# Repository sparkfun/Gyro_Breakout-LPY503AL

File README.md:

SparkFun Gyro Breakout - LPY503AL (Dual 30°/s)
========================================

[*SparkFun Gyro Breakout - LPY503AL (Dual 30°/s) (SEN-11341)*](https://www.sparkfun.com/products/11341)

This is a breakout board for the ST’s dual-axis LPY503AL gyro.  
The LPY503AL is a MEMS motion sensor that measures angular velocity along the pitch and yaw axes with a full scale of ±30°/s. 
Two different analog outputs are provided for both the x- and z- axes - one 1x amplified and the other 4x amplified.

Repository Contents
-------------------

* **/Hardware** - Eagle design files (.brd, .sch)
* **/Production** - Production panel files (.brd)

Documentation
--------------
* **[SparkFun Fritzing repo](https://github.com/sparkfun/Fritzing_Parts)** - Fritzing diagrams for SparkFun products.
* **[SparkFun 3D Model repo](https://github.com/sparkfun/3D_Models)** - 3D models of SparkFun products. 

License Information
-------------------
This product is _**open source**_! 

The **hardware** is released under [Creative Commons ShareAlike 4.0 International](https://creativecommons.org/licenses/by-sa/4.0/).

Please use, reuse, and modify these files as you see fit. Please maintain attribution to SparkFun Electronics and release anything derivative under the same license.

Distributed as-is; no warranty is given.

- Your friends at SparkFun.

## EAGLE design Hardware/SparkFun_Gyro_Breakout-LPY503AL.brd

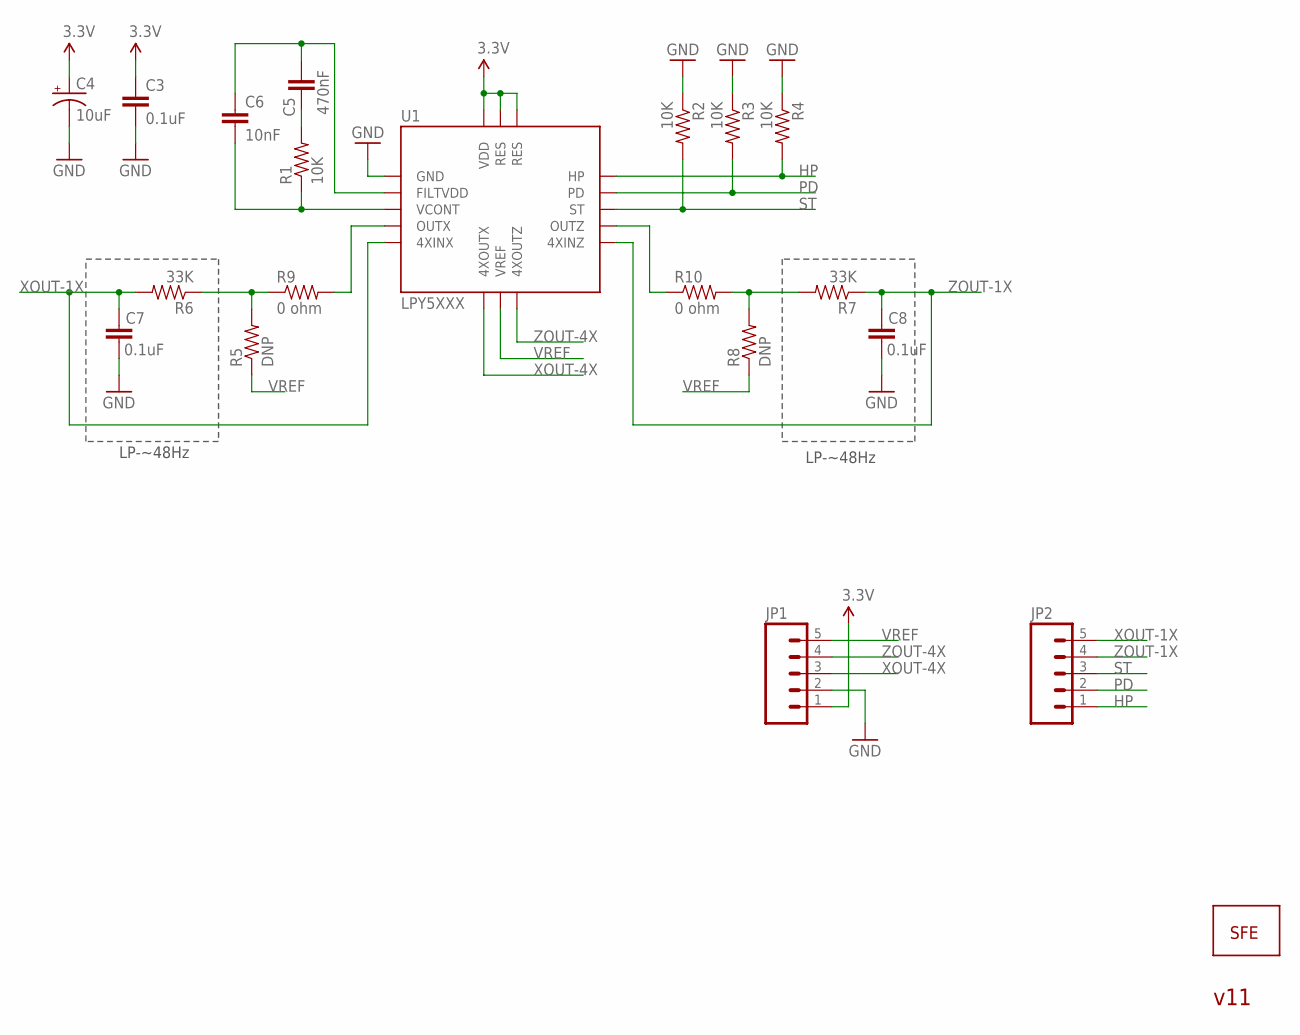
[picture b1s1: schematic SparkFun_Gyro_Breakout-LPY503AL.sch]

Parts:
C3, C7, C8: 0.1uF; 0402-CAP
C4: 10uF; EIA3216
C5: 470nF; 0402-CAP
C6: 10nF; 0402-CAP
JP1, JP2: M05PTH; 1X05
R1, R2, R3, R4: 10K; 0402-RES
R5, R8: DNP; 0402-RES
R6, R7: 33K; 0402-RES
R9, R10: 0 ohm; 0402-RES
U1: LPY5XXX; ST-GYRO
U$1: LOGO-SFESK; SFE-LOGO-FLAME

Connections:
3.3V: C3.1, C4.A (+), JP1.1, U1.14 (RES), U1.15 (RES), U1.16 (VDD)
F1: C5.1, C6.1, U1.2 (FILTVDD)
F2: C6.2, R1.1, U1.3 (VCONT)
GND: C3.2, C4.C (-), C7.1, C8.1, JP1.2, R2.1, R3.1, R4.1, U1.1 (GND)
HP: JP2.1, R4.2, U1.13 (HP)
unnamed: R9.2, U1.4 (OUTX)
unnamed: C5.2, R1.2
unnamed: R10.1, U1.10 (OUTZ)
unnamed: R5.2, R6.1, R9.1
unnamed: R7.2, R8.2, R10.2
PD: JP2.2, R3.2, U1.12 (PD)
ST: JP2.3, R2.2, U1.11 (ST)
VREF: JP1.5, R5.1, R8.1, U1.7 (VREF)
XOUT-1X: C7.2, JP2.5, R6.2, U1.5 (4XINX)
XOUT-4X: JP1.3, U1.6 (4XOUTX)
ZOUT-1X: C8.2, JP2.4, R7.1, U1.9 (4XINZ)
ZOUT-4X: JP1.4, U1.8 (4XOUTZ)

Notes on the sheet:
LP-~48Hz
v11

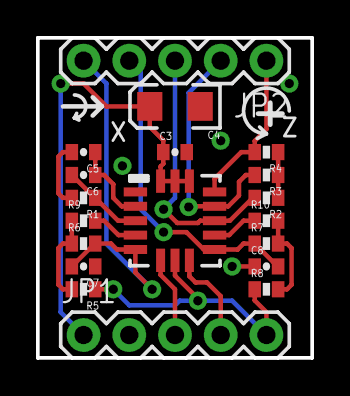
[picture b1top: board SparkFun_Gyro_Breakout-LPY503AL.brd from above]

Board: 2 copper layers, 15.2 x 17.8 mm, 20 parts (1 on the bottom side), 17 nets.

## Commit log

2015-05-06 Adding hardware files, updating README
